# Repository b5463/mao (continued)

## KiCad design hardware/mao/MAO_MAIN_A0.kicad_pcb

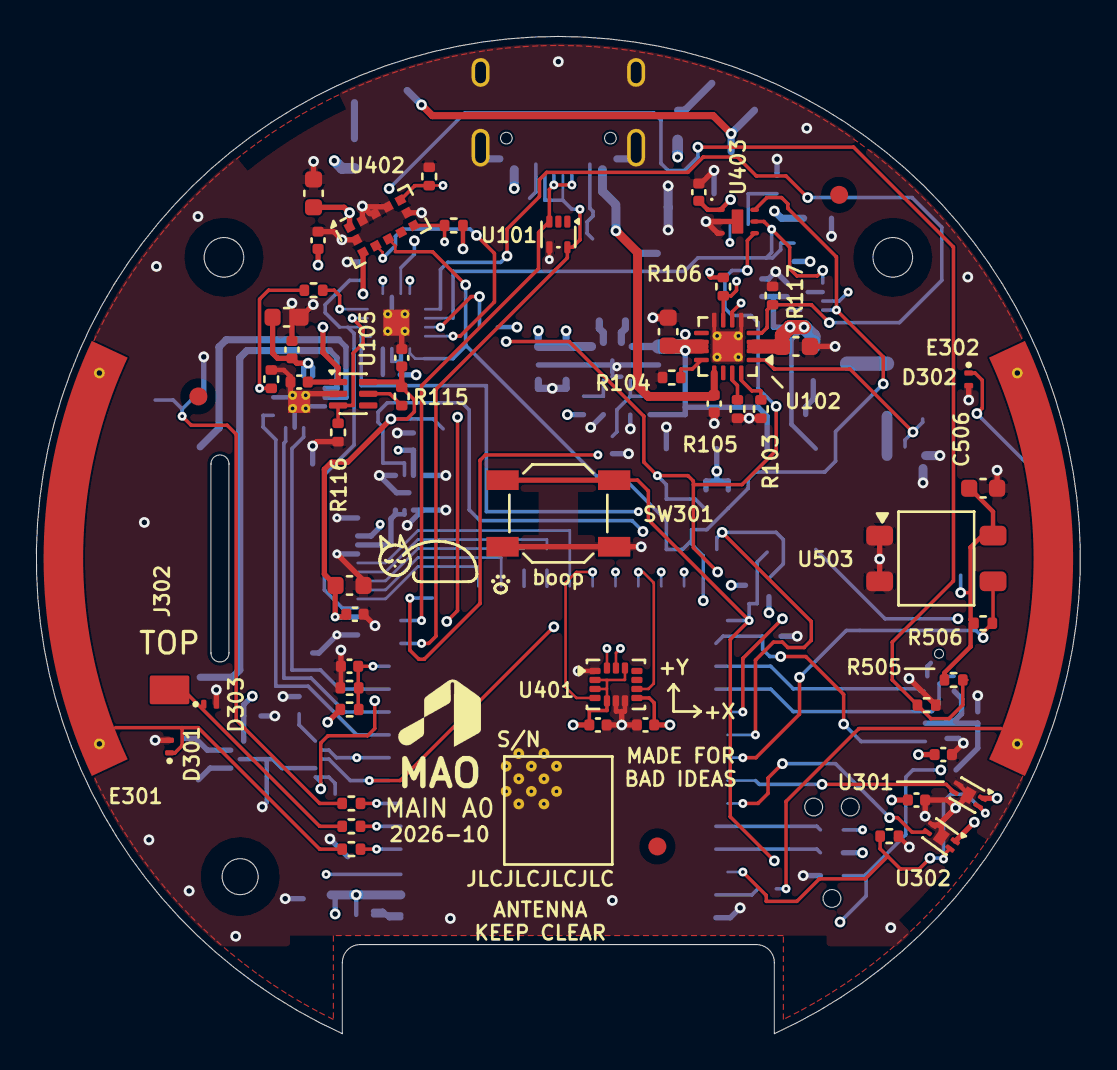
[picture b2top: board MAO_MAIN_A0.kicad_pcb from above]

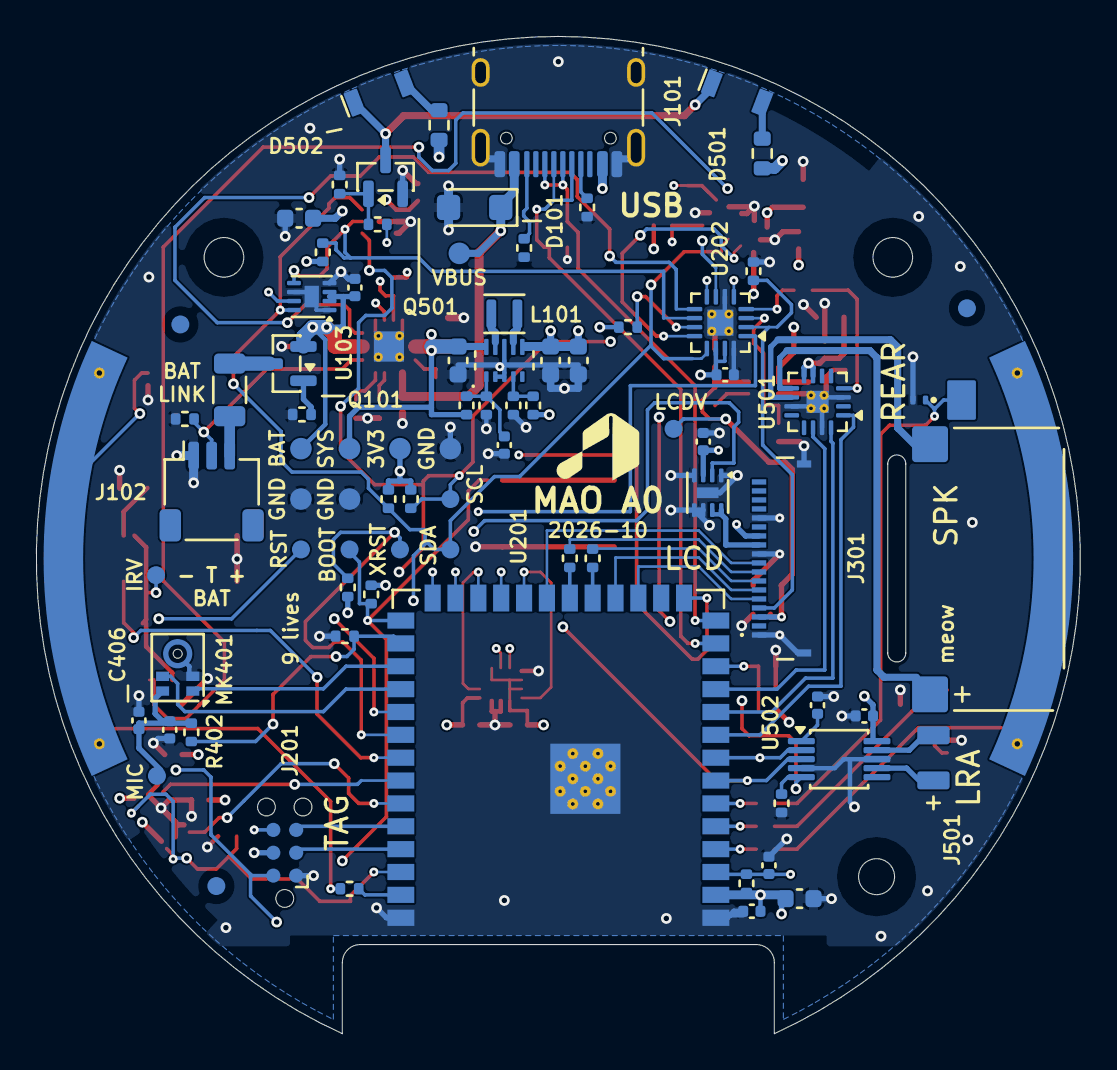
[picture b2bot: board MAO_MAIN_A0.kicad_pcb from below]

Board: 4 copper layers, 58.0 x 55.4 mm, 142 parts (82 on the bottom side), 83 nets.

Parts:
C101, C109, C110, C203, C305, C406, C503, C504: 1uF 25V; C_0402_1005Metric
C102, C103, C105, C501, C505: 10uF 10V; C_0603_1608Metric
C104, C111, C202, C204, C205, C301, C303, C304, C401, C402, C403, C405, C407, C502: 100nF 16V; C_0402_1005Metric
C106, C107, C201: 22uF 6.3V; C_0603_1608Metric
C302, C404, C506: 4.7uF 16V; C_0603_1608Metric
D101: SMF15A; D_SMF
D301, D302, D303, D304: TPD1E05U06; Texas_DPY0002A_0.6x1mm_P0.65mm
D501, D502: IR12-21C; Everlight_IR12-21C_RightAngle_3x1mm
E301: TOUCH LEFT; TouchArc_R26.4-28.6_50deg
E302: TOUCH RIGHT; TouchArc_R26.4-28.6_50deg
FID1, FID2, FID3, FID4, FID5, FID6: FID; Fiducial_1mm_Mask2mm
H1, H2: MOUNT; MountingHole_2.2mm_M2
H3: MOUNT; MountingHole_2mm
J101: USB-C; USB_C_Receptacle_HRO_TYPE-C-31-M-12
J102: BAT; JST_SH_SM03B-SRSS-TB_1x03-1MP_P1.00mm_Horizontal
J201: TAG; Tag-Connect_TC2030-IDC-NL_2x03_P1.27mm_Vertical
J301: LCD; HDGC_0.5K-HX-18PWB_1x18-1MP_P0.5mm_Horizontal
J302: TOUCH TOP; BAT_BW0019BG_SpringContact_3.5x1.5mm
J303: TOUCH REAR; BAT_BW0019BG_SpringContact_3.5x1.5mm
J501: LRA; WirePads_1x02_P2.5mm_1.0x1.8mm
L101: 0.47uH; L_Murata_DFE201610P
LS501: CMS-150803-088S-X8; SameSky_CMS-150803_SpringPads
MK401: SPH0641LU4H-1; Knowles_LGA-5_3.5x2.65mm
Q101: AO3401A; SOT-23
Q501: AO3400A; SOT-23
R101, R102: 5.1k; R_0402_1005Metric
R103: 4.3k; R_0402_1005Metric
R104: 1.5k; R_0402_1005Metric
R105: 0R; R_0402_1005Metric
R106, R114, R116, R117, R206, R207, R208, R209, R210, R211, R212, R306, R403, R504: 100k; R_0402_1005Metric
R108: 0R; R_1206_3216Metric
R109, R110, R201, R202, R205, R401, R506: 10k; R_0402_1005Metric
R111: 470k; R_0402_1005Metric
R112: 240k; R_0402_1005Metric
R113: 536k; R_0402_1005Metric
R115, R402, R503, R505: 100R; R_0402_1005Metric
R203, R204: 1M; R_0402_1005Metric
R213, R214, R507: 2.2k; R_0402_1005Metric
R301, R302: 22R; R_0402_1005Metric
R307, R308, R309, R310: 510R; R_0402_1005Metric
R501, R502: 56R; R_0603_1608Metric
SW301: SKQGADE010; SW_SPST_SKQG_WithStem
TP1, TP2, TP16: GND; TestPoint_Pad_D1.2mm
TP3: 3V3; TestPoint_Pad_D1.2mm
TP4: SYS; TestPoint_Pad_D1.2mm
TP5: BAT; TestPoint_Pad_D1.2mm
TP6: VBUS; TestPoint_Pad_D1.2mm
TP7: RST; TestPoint_Pad_D1.0mm
TP8: BOOT; TestPoint_Pad_D1.0mm
TP9: SDA; TestPoint_Pad_D1.0mm
TP10: SCL; TestPoint_Pad_D1.0mm
TP11: XRST; TestPoint_Pad_D1.0mm
TP13: LCDV; TestPoint_Pad_D1.0mm
TP14: MIC; TestPoint_Pad_D1.0mm
TP15: IRV; TestPoint_Pad_D1.0mm
U101: TPD2E2U06; SOT-553
U102: BQ24073RGTR; VQFN-16-1EP_3x3mm_P0.5mm_EP1.68x1.68mm_ThermalVias
U103: MAX17048G+T10; TDFN-8-1EP_2x2mm_P0.5mm_EP0.8x1.2mm
U104: TPS63802DLAR; TI_DLA0010A_VSON-HR-10_2x3mm_P0.5mm
U105: TPS22919DCKR; SOT-363_SC-70-6
U201: ESP32-S3-WROOM-1-N8R2; ESP32-S3-WROOM-1
U202: TCA6408ARGTR; VQFN-16-1EP_3x3mm_P0.5mm_EP1.45x1.45mm_ThermalVias
U301, U302: DRV5012AEDMRR; Texas_X2SON-4-1EP_1.1x1.4mm_P0.5mm_EP0.8x0.6mm
U303: AW9364DNR; DFN-8-1EP_2x2mm_P0.5mm_EP0.6x1.2mm
U401: LSM6DSOXTR; LGA-14_3x2.5mm_P0.5mm_LayoutBorder3x4y
U402: VL53L4CDV0DH/1; ST_VL53L0X
U403: OPT3004DNPR; TI_DNP0006A_USON-6_2x2mm_P0.65mm_EP0.65x1.35mm
U501: MAX98357AETE+T; TQFN-16-1EP_3x3mm_P0.5mm_EP1.23x1.23mm_ThermalVias
U502: DRV2605LDGSR; MSOP-10_3x3mm_P0.5mm
U503: IRM-H638T/TR2; Everlight_IRM-H6xxT

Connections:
3V3_LCD: C109.1, C301.1, C302.1, J301.3, R115.2, TP13.1, U105.6
+3V3: C106.1, C107.1, C110.1, C201.1, C202.1, C205.1, C303.1, C304.1, C401.1, C402.1, C403.1, C404.1, C405.1, J201.4, R106.2, R113.1, R201.1, R202.1, R203.1, R205.1, R206.1, R212.1, R213.1, R214.1, R401.1, TP3.1, U102.6, U104.6, U105.1, U201.2, U202.14, U202.15, U301.1, U302.1, U401.2, U401.3, U401.5, U401.8, U401.12, U402.1, U402.11, U403.1
AMP_BCLK: U201.10, U501.16
AMP_DIN: U201.9, U501.1
AMP_LRCLK: U201.11, U501.14
AMP_SD: R208.1, R507.2, U501.4
AMP_SD_N: R507.1, U202.4
BAT_IN: Q101.3, R108.2
BAT_NTC: J102.2, R110.1, U102.1
BAT_RAW: J102.3, R108.1
BAT_RPP_G: Q101.1, R109.1
BB_EN: C111.1, R111.2, R112.1, U104.1
BB_FB: R113.2, R114.1, U104.4
BB_L1: L101.1, U104.9
BB_L2: L101.2, U104.7
BOARD_ID: C204.1, R203.2, R204.1, U201.12
CHG_CE_N: R117.1, U102.4, U202.9
CHG_ILIM: R104.1, U102.12
CHG_ISET: R103.1, U102.16
CHG_TD: R105.1, U102.15
EXP_INT_N: R206.2, U201.23, U202.11
EXP_RST_N: R205.2, TP11.1, U201.32, U202.1
GND: C101.2, C102.2, C103.2, C104.2, C105.2, C106.2, C107.2, C109.2, C110.2, C111.2, C201.2, C202.2, C203.2, C204.2, C205.2, C301.2, C302.2, C303.2, C304.2, C305.2, C401.2, C402.2, C403.2, C404.2, C405.2, C406.2, C407.2, C501.2, C502.2, C503.2, C504.2, C505.2, C506.2, D101.2, D301.2, D302.2, D303.2, D304.2, J101.A1, J101.A12, J101.B1, J101.B12, J101.SH, J102.1, J201.1, J301.1, J301.10, J301.14, J301.MP, MK401.2, MK401.3, Q501.2, R101.2, R102.2, R103.2, R104.2, R105.2, R109.2, R110.2, R112.2, R114.2, R116.2, R117.2, R204.2, R207.2, R208.2, R209.2, R210.2, R211.2, R306.2, R403.2, R504.2, SW301.2, TP1.1, TP2.1, TP16.1, U101.4, U102.5, U102.8, U102.17, U103.1, U103.4, U103.6, U103.9, U104.2, U104.3, U104.8, U105.2, U201.1, U201.40, U201.41, U202.6, U202.16, U202.17, U301.2, U301.5, U302.2, U302.5, U303.1, U303.4, U303.5, U303.6, U303.9, U401.1, U401.6, U401.7, U402.2, U402.3, U402.4, U402.6, U402.12, U403.2, U403.3, U403.7, U501.3, U501.11, U501.15, U501.17, U502.4, U502.8, U503.1, U503.2
HALL_A: U201.34, U301.3
HALL_B: U201.35, U302.3
HALL_FAST: R306.1, U201.38, U301.4, U302.4
HAPTIC_EN: R209.1, U202.5, U502.5
HAP_REG: C504.1, U502.1
I2C_SCL: R214.2, TP10.1, U103.7, U201.8, U202.12, U401.13, U402.10, U403.4, U502.2
I2C_SDA: R213.2, TP9.1, U103.8, U201.7, U202.13, U401.14, U402.9, U403.6, U502.3
IMU_INT1: U201.22, U401.4
IMU_INT2: U201.24, U401.9
IR_LED_A1: D501.2, R501.2
IR_LED_A2: D502.2, R502.2
IR_LED_K: D501.1, D502.1, Q501.3
IR_RX: R506.2, U201.33, U503.3
IR_RX_PWR: R211.1, R505.1, U202.8
IR_RX_VCC: C506.1, R505.2, R506.1, TP15.1, U503.4
IR_TX: R503.1, U201.31
IR_TX_G: Q501.1, R503.2, R504.1
LCD_BL_CTRL: U201.26, U303.2
LCD_BL_K: J301.11, U303.7, U303.8
LCD_CS: J301.9, U201.21
LCD_DC: J301.6, U201.18
LCD_MOSI: R302.1, U201.19
LCD_MOSI_P: J301.7, R302.2
LCD_PWR_EN: R116.1, U105.3, U202.3
LCD_RST_N: J301.4, R207.1, U202.2
LCD_SCLK: R301.1, U201.20
LCD_SCLK_P: J301.8, R301.2
LCD_SW_QOD: R115.1, U105.5
LCD_TE: J301.5, U201.17
LRA_N: J501.2, U502.9
LRA_P: J501.1, U502.7
MCU_EN: C203.1, J201.2, R201.2, TP7.1, U201.3
MIC_CLK: MK401.4, U201.30
MIC_DATA: MK401.1, U201.29
MIC_PWR: R402.1, R403.1, U201.28
MIC_VDD: C406.1, C407.1, MK401.5, R402.2, TP14.1
PRESS_N: J201.6, R202.2, SW301.1, TP8.1, U201.27
SENSE_ALRT_N: R212.2, U103.5, U202.10, U403.5
SPK_N: LS501.2, U501.10
SPK_P: LS501.1, U501.9
TOF_INT_N: R401.2, U201.25, U402.7
TOF_XSHUT: R210.1, U202.7, U402.5
TOUCH_LEFT: R307.1, U201.4
TOUCH_LEFT_E: D301.1, E301.1, R307.2
TOUCH_REAR: R310.1, U201.6
TOUCH_REAR_E: D304.1, J303.1, R310.2
TOUCH_RIGHT: R308.1, U201.39
TOUCH_RIGHT_E: D302.1, E302.1, R308.2
TOUCH_TOP: R309.1, U201.5
TOUCH_TOP_E: D303.1, J302.1, R309.2
UART_RX: J201.5, U201.36
UART_TX: J201.3, U201.37
USB_CC1: J101.A5, R101.1
USB_CC2: J101.B5, R102.1
USB_DN: J101.A7, J101.B7, U101.5, U201.13
USB_DP: J101.A6, J101.B6, U101.3, U201.14
USB_PRESENT_N: R106.1, U102.7, U201.15
VBAT: C103.1, C104.1, Q101.2, TP5.1, U102.2, U102.3, U103.2, U103.3
VBUS: C101.1, D101.1, J101.A4, J101.A9, J101.B4, J101.B9, TP6.1, U102.13
VSYS: C102.1, C105.1, C305.1, C501.1, C502.1, C503.1, C505.1, J301.12, R111.1, R501.1, R502.1, TP4.1, U102.10, U102.11, U104.10, U303.3, U501.7, U501.8, U502.10

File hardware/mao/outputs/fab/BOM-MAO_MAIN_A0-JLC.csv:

Comment,Designator,Footprint,LCSC Part #,Manufacturer Part,Manufacturer,Quantity
1uF 25V,"C101,C109,C110,C203,C305,C406,C503,C504",C_0402_1005Metric,C52923,CL05A105KA5NQNC,Samsung,8
10uF 10V,"C102,C103,C105,C501,C505",C_0603_1608Metric,C19702,CL10A106KP8NNNC,Samsung,5
100nF 16V,"C104,C111,C202,C204,C205,C301,C303,C304,C401,C402,C403,C405,C407,C502",C_0402_1005Metric,C1525,CL05B104KO5NNNC,Samsung,14
22uF 6.3V,"C106,C107,C201",C_0603_1608Metric,C59461,CL10A226MQ8NRNC,Samsung,3
4.7uF 16V,"C302,C404,C506",C_0603_1608Metric,C19666,CL10A475KO8NNNC,Samsung,3
SMF15A,D101,D_SMF,C123802,SMF15A,MDD,1
TPD1E05U06,"D301,D302,D303,D304",Texas_DPY0002A_0.6x1mm_P0.65mm,C436349,TPD1E05U06DPYR,TI,4
IR12-21C,"D501,D502",Everlight_IR12-21C_RightAngle_3x1mm,C53672,IR12-21C/TR8,Everlight,2
USB-C,J101,USB_C_Receptacle_HRO_TYPE-C-31-M-12,C165948,TYPE-C-31-M-12,Korean Hroparts,1
BAT,J102,JST_SH_SM03B-SRSS-TB_1x03-1MP_P1.00mm_Horizontal,C7430445,ZX-SH1.0-3PWT (JST SM03B-SRSS-TB compatible),Megastar,1
LCD,J301,HDGC_0.5K-HX-18PWB_1x18-1MP_P0.5mm_Horizontal,C2919497,0.5K-HX-18PWB,HDGC,1
BW0019BG-L3.5W1.5H3.8,"J302,J303",BAT_BW0019BG_SpringContact_3.5x1.5mm,C2826516,BW0019BG-L3.5W1.5H3.8,BAT WIRELESS,2
0.47uH,L101,L_Murata_DFE201610P,C668312,DFE201612E-R47M=P2,Murata,1
SPH0641LU4H-1,MK401,Knowles_LGA-5_3.5x2.65mm,C2879853,SPH0641LU4H-1,Knowles,1
AO3401A,Q101,SOT-23,C15127,AO3401A,AOS,1
AO3400A,Q501,SOT-23,C20917,AO3400A,AOS,1
5.1k,"R101,R102",R_0402_1005Metric,C25905,0402WGF5101TCE,UNI-ROYAL,2
4.3k,R103,R_0402_1005Metric,C25899,0402WGF4301TCE,UNI-ROYAL,1
1.5k,R104,R_0402_1005Metric,C25867,0402WGF1501TCE,UNI-ROYAL,1
0R,R105,R_0402_1005Metric,C17168,0402WGF0000TCE,UNI-ROYAL,1
100k,"R106,R114,R116,R117,R206,R207,R208,R209,R210,R211,R212,R306,R403,R504",R_0402_1005Metric,C25741,0402WGF1003TCE,UNI-ROYAL,14
0R,R108,R_1206_3216Metric,C17888,1206W4F0000T5E,UNI-ROYAL,1
10k,"R109,R201,R202,R205,R401,R506",R_0402_1005Metric,C25744,0402WGF1002TCE,UNI-ROYAL,6
470k,R111,R_0402_1005Metric,C25790,0402WGF4703TCE,UNI-ROYAL,1
240k,R112,R_0402_1005Metric,C64043,0402WGF2403TCE,UNI-ROYAL,1
536k,R113,R_0402_1005Metric,C68457,0402WGF5363TCE,UNI-ROYAL,1
100R,"R115,R402,R503,R505",R_0402_1005Metric,C25076,0402WGF1000TCE,UNI-ROYAL,4
1M,"R203,R204",R_0402_1005Metric,C26083,0402WGF1004TCE,UNI-ROYAL,2
2.2k,"R213,R214,R507",R_0402_1005Metric,C25879,0402WGF2201TCE,UNI-ROYAL,3
22R,"R301,R302",R_0402_1005Metric,C25092,0402WGF220JTCE,UNI-ROYAL,2
510R,"R307,R308,R309,R310",R_0402_1005Metric,C25123,0402WGF5100TCE,UNI-ROYAL,4
56R,"R501,R502",R_0603_1608Metric,C25196,0603WAF560JT5E,UNI-ROYAL,2
SKQGADE010,SW301,SW_SPST_SKQG_WithStem,C116647,SKQGADE010,ALPS,1
TPD2E2U06,U101,SOT-553,C1972959,TPD2E2U06DRLR,TI,1
BQ24073RGTR,U102,VQFN-16-1EP_3x3mm_P0.5mm_EP1.68x1.68mm_ThermalVias,C15220,BQ24073RGTR,TI,1
MAX17048G+T10,U103,TDFN-8-1EP_2x2mm_P0.5mm_EP0.8x1.2mm,C2682616,MAX17048G+T10,Analog Devices,1
TPS63802DLAR,U104,TI_DLA0010A_VSON-HR-10_2x3mm_P0.5mm,C2845237,TPS63802DLAR,TI,1
TPS22919DCKR,U105,SOT-363_SC-70-6,C2149796,TPS22919DCKR,TI,1
ESP32-S3-WROOM-1-N8R2,U201,ESP32-S3-WROOM-1,C2913204,ESP32-S3-WROOM-1-N8R2,Espressif,1
TCA6408ARGTR,U202,VQFN-16-1EP_3x3mm_P0.5mm_EP1.45x1.45mm_ThermalVias,C181499,TCA6408ARGTR,TI,1
DRV5012AEDMRR,"U301,U302",Texas_X2SON-4-1EP_1.1x1.4mm_P0.5mm_EP0.8x0.6mm,C2655038,DRV5012AEDMRR,TI,2
AW9364DNR,U303,DFN-8-1EP_2x2mm_P0.5mm_EP0.6x1.2mm,C401007,AW9364DNR,Awinic,1
LSM6DSOXTR,U401,LGA-14_3x2.5mm_P0.5mm_LayoutBorder3x4y,C481766,LSM6DSOXTR,ST,1
VL53L4CDV0DH/1,U402,ST_VL53L0X,C3178291,VL53L4CDV0DH/1,ST,1
OPT3004DNPR,U403,TI_DNP0006A_USON-6_2x2mm_P0.65mm_EP0.65x1.35mm,C2655153,OPT3004DNPR,TI,1
MAX98357AETE+T,U501,TQFN-16-1EP_3x3mm_P0.5mm_EP1.23x1.23mm_ThermalVias,C910544,MAX98357AETE+T,Analog Devices,1
DRV2605LDGSR,U502,MSOP-10_3x3mm_P0.5mm,C527464,DRV2605LDGSR,TI,1
IRM-H638T/TR2,U503,Everlight_IRM-H6xxT,C91447,IRM-H638T/TR2,Everlight,1

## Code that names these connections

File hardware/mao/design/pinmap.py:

"""MAO_MAIN A1 authoritative pin map (ODD JOBS 199).

One table drives three things: the schematic nets of the module (circuit.py), the firmware board
header (hardware/mao/design/gen_pinmap.py writes
components/mao_board/boards/main_a1/mao_board_pins.h) and docs/hardware/mao-pin-map.md.
Change a pin here and regenerate; never edit the generated outputs.

A1 = A0 moved to the M5 Gate C locked architecture (docs/hardware/m5_0_gate_c.md):
ESP32-S3-MINI-1-N8 (no PSRAM; IO22-25 and IO27-32 are not brought out), no I/O expander (its
lines are native GPIOs now), no touch, no microphone, no ambient-light sensor, no board-ID divider
(the revision is written to NVS at manufacturing).

Rules this table keeps (Gate A/B.1/C):
  * the face press and one dial line are RTC wake inputs, and the press is NOT on a strap
    (GPIO0 is only the BOOT pad now);
  * every default-off enable sits on GPIO1-21 or 38, which have no pull at reset (S3 datasheet
    v2.2 Table 2-1); GPIO39-42 (JTAG pads) and GPIO33/34 have reset pull-ups and carry only
    inputs or I2S lines whose consumer is held off;
  * nothing may pull GPIO45 high at reset (VDD_SPI = 1.8 V would stop the 3.3 V flash);
  * >= 4 spare pins: GPIO26, GPIO39, GPIO43/44 (UART0 service pads).

Routing swaps (2026-10-06, A1 layout): the first A1 layout could not route the board with the pin map as
committed: the face press (GPIO1) sat at the module's far corner from the switch, the dial's wake line (GPIO2)
on the side away from the Hall pair, the IR receiver's enable (GPIO16) away from its switch and the ToF
interrupt (GPIO38) away from the sensor. Swapped, every rule above kept: PRESS_N GPIO1 -> GPIO14 (RTC, not a
strap), HAPTIC_EN GPIO14 -> GPIO1 (reset-quiet enable pin), HALL_A GPIO2 -> GPIO21 (RTC: ext0 wake), the spare
GPIO21 -> GPIO2, AUX_PWR_EN GPIO16 -> GPIO38 (reset-quiet), TOF_INT_N GPIO38 -> GPIO16.

USB wake (design review 2026-10-06, finding 1): VBUS_SENSE on GPIO39 could not wake A1 from deep sleep (GPIO39 is
not an RTC pad). The VBUS divider now drives the gate of a 2N7002 whose drain, USB_PRESENT_N (100k pull-up to +3V3,
33 uA only while USB is present), is the spare RTC pad GPIO2: an ext1 any-low wake source. GPIO39 becomes a spare
with its own test pad.

Module pin numbers are ESP32-S3-MINI-1 pads (datasheet v1.7 Table 3-1).
"""

# (gpio, net, direction, function, notes)
#   direction: in / out / io / od (open-drain input) / analog
#   flags in notes: R = RTC GPIO (deep-sleep wake/hold), S = strapping pin
NATIVE = [
    (0,  None,          'nc',  'BOOT strap (pad only)', 'S R; 10k pull-up, TP BOOT: the fixture holds it low for download. Nothing else on it'),
    (1,  'HAPTIC_EN',   'out', 'haptic driver enable', 'R; 100k pull-down (+ the DRV2605L\'s internal 2M): off'),
    (2,  'USB_PRESENT_N', 'od', 'USB present, active low (VBUS divider -> 2N7002 inverter)', 'R; 100k pull-up at the FET drain (33 uA only while USB is present, 0 uA on battery); deep-sleep wake (ext1, any-low; armed only while it idles high)'),
    (3,  None,          'nc',  'JTAG-source strap', 'S; NC (inert unless EFUSE_STRAP_JTAG_SEL is burnt, never on MAO)'),
    (4,  'IMU_INT1',    'od',  'IMU INT1: wake-on-motion (ICM-42670-P, open-drain, active low, latched)', 'R; 100k pull-up; deep-sleep wake (ext1, any-low)'),
    (5,  'HALL_FAST',   'out', 'Hall sensors: high = fast sampling, low = low-power', 'R; 100k pull-down: low-power from reset and in deep sleep'),
    (6,  'LCD_PWR_EN',  'out', 'display logic rail switch (TPS22916C)', 'R; switch\'s smart pull-down + 100k: panel unpowered from reset'),
    (7,  'LCD_RST_N',   'out', 'display reset', 'R; 100k pull-down: panel held in reset'),
    (8,  'LCD_BL',      'out', 'backlight current-sink reference (LEDC ~30 kHz)', 'R; 100k pull-down + divider: dark from reset'),
    (9,  'AMP_SD',      'out', 'amplifier SD_MODE (high = on, left channel)', 'R; 100k pull-down + the MAX98357A\'s internal 100k: silent from reset'),
    (10, 'LCD_CS',      'out', 'display chip select (FSPICS0 IO_MUX)', 'R'),
    (11, 'LCD_MOSI',    'out', 'display data (FSPID IO_MUX)', 'R; 22R series'),
    (12, 'LCD_SCLK',    'out', 'display clock (FSPICLK IO_MUX)', 'R; 22R series'),
    (13, 'LCD_DC',      'out', 'display data/command', 'R'),
    (14, 'PRESS_N',     'in',  'face-press switch (to GND)', 'R; 100k pull-up (draws only while pressed); deep-sleep wake (ext1, any-low)'),
    (15, 'TOF_XSHUT',   'out', 'proximity sensor shutdown (low = off)', 'R; 100k pull-down: off'),
    (16, 'TOF_INT_N',   'od',  'proximity GPIO1: threshold interrupt', 'R; 10k pull-up (ST application circuit)'),
    (17, 'IR_TX',       'out', 'IR LED driver gate (RMT carrier)', 'R; 100k pull-down: LEDs off at reset'),
    (18, 'CHG_CE_N',    'out', 'charger /CE: high pauses charging (firmware thermal limit, cell 0-45 C)', 'R; 100k pull-down: charging enabled from reset'),
    (19, 'USB_DN',      'io',  'USB D-', 'native USB-Serial/JTAG; 22R series + DNP 10 pF'),
    (20, 'USB_DP',      'io',  'USB D+', 'native USB-Serial/JTAG; 22R series + DNP 10 pF'),
    (21, 'HALL_A',      'in',  'ring dial channel A', 'R; push-pull from the Hall latch; deep-sleep wake (ext0, armed at the opposite level)'),
    (26, None,          'nc',  'spare', 'free on the -N8 (SPICS1 only on -N4R2); test pad'),
    (33, 'CHG_STAT1',   'od',  'charger STAT1 (open-drain)', '10k pull-up; both STAT pins high-Z on battery: 0 uA'),
    (34, 'CHG_STAT2',   'od',  'charger STAT2 (open-drain)', '10k pull-up'),
    (35, 'LCD_TE',      'in',  'display tearing-effect output: frame sync', 'driven by the panel; isolated while the panel is off'),
    (36, 'IR_RX',       'in',  'IR receiver output (RMT)', 'receiver supply switched by AUX_PWR_EN; isolated while it is off. IMU INT2 is not wired on A1: INT1 carries wake-on-motion, the rest is polled'),
    (37, 'HALL_B',      'in',  'ring dial channel B', 'push-pull from the Hall latch'),
    (38, 'AUX_PWR_EN',  'out', 'IR receiver supply switch (TPS22916C on +3V3)', 'no reset pull; switch\'s smart pull-down + 100k: off'),
    (39, None,          'nc',  'spare', 'test pad (TP26); JTAG MTCK pad with a reset pull-up'),
    (40, 'AMP_BCLK',    'out', 'I2S bit clock to the amplifier', ''),
    (41, 'AMP_LRCLK',   'out', 'I2S word select', ''),
    (42, 'AMP_DIN',     'out', 'I2S data', ''),
    (43, 'UART_TX',     'out', 'UART0 TX (service / spare)', 'service pad; the ROM prints here at reset'),
    (44, 'UART_RX',     'in',  'UART0 RX (service / spare)', 'service pad'),
    (45, None,          'nc',  'VDD_SPI strap', 'S; NC with its internal pull-down: 3.3 V flash. Nothing may pull it high'),
    (46, None,          'nc',  'boot-mode strap', 'S; NC with its internal pull-down'),
    (47, 'I2C_SDA',     'io',  'I2C data (IMU, ToF, gauge, haptic)', '4.7k pull-up to +3V3; VDD_SPI/VDD3P3_CPU domain = 3.3 V on the N8'),
    (48, 'I2C_SCL',     'out', 'I2C clock', '4.7k pull-up to +3V3'),
]

# A1 has no I/O expander (its lines are native above).
EXPANDER = []

I2C_ADDRESSES = {
    0x29: 'VL53L4CD proximity (default)',
    0x36: 'MAX17048 fuel gauge',
    0x5A: 'DRV2605L haptic driver',
    0x68: 'ICM-42670-P IMU (AP_AD0 low)',
}

# MINI-1 pads that are GPIOs (Table 3-1): the checks below make sure every one is accounted for.
MODULE_GPIOS = list(range(0, 22)) + [26] + list(range(33, 49))
SPARES_MIN = 4


def native_by_net():
    return {net: gpio for gpio, net, *_ in NATIVE if net}


def expander_by_net():
    return {}


def _self_check():
    gpios = [g for g, *_ in NATIVE]
    assert sorted(gpios) == MODULE_GPIOS, 'every MINI-1 GPIO exactly once'
    nets = [n for _, n, *_ in NATIVE if n]
    assert len(nets) == len(set(nets)), 'a net on two pins'
    assert native_by_net().get('PRESS_N') not in (0, 3, 45, 46), 'press on a strap'
    for net in ('PRESS_N', 'HALL_A', 'IMU_INT1', 'USB_PRESENT_N'):
        assert native_by_net()[net] <= 21, net + ' must be an RTC GPIO (wake)'
    enables = ('HALL_FAST', 'LCD_PWR_EN', 'LCD_RST_N', 'LCD_BL', 'AMP_SD', 'HAPTIC_EN', 'TOF_XSHUT',
               'AUX_PWR_EN', 'IR_TX', 'CHG_CE_N')
    for net in enables:
        g = native_by_net()[net]
        assert 1 <= g <= 21 or g == 38, net + ' needs a pin without a reset pull'
    spare = [g for g, n, *_ in NATIVE if n is None and g not in (0, 3, 45, 46)]
    spare += [native_by_net()[n] for n in ('UART_TX', 'UART_RX')]
    assert len(spare) >= SPARES_MIN, 'fewer than %d spares' % SPARES_MIN


_self_check()
